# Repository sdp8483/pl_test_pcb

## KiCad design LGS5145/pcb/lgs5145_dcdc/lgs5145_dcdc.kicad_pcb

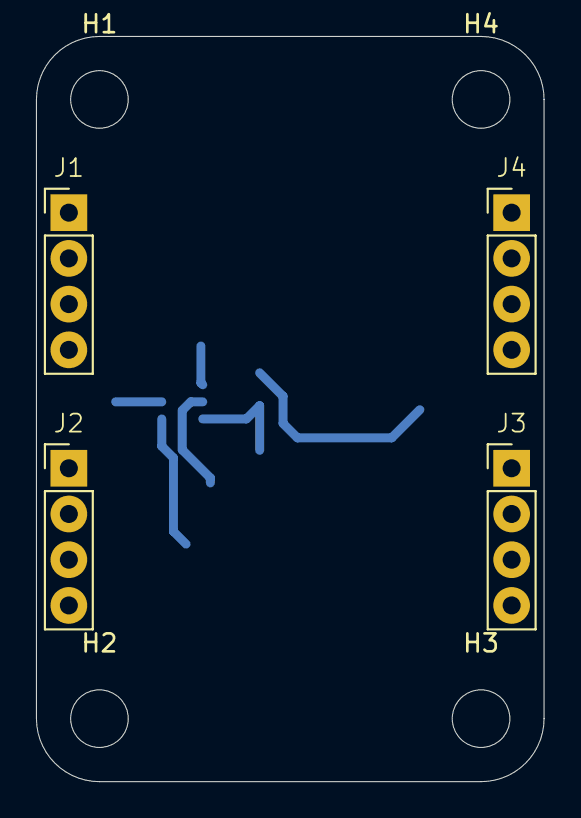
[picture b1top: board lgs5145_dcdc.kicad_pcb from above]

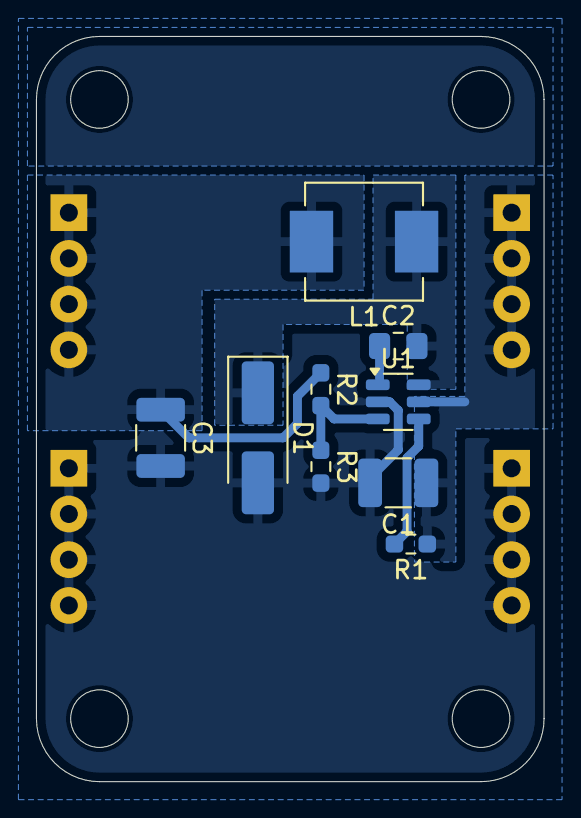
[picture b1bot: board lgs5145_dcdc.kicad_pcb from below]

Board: 2 copper layers, 28.2 x 41.4 mm, 17 parts (9 on the bottom side), 7 nets.

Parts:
C1, C3: 10uF; C_1210_3225Metric_Pad1.33x2.70mm_HandSolder
C2: 100nF; C_0805_2012Metric_Pad1.18x1.45mm_HandSolder
D1: SS56; D_SMA_Handsoldering
H1, H2, H3, H4: MountingHole; MountingHole_3.2mm_M3
J1: IN; PinHeader_1x04_P2.54mm_Vertical
J2, J3: GND; PinHeader_1x04_P2.54mm_Vertical
J4: OUT; PinHeader_1x04_P2.54mm_Vertical
L1: L; L_Vishay_IHLP-2525
R1: 10k; R_0603_1608Metric_Pad0.98x0.95mm_HandSolder
R2: 82k; R_0603_1608Metric_Pad0.98x0.95mm_HandSolder
R3: 16k; R_0603_1608Metric_Pad0.98x0.95mm_HandSolder
U1: LGS5145; SOT-23-6

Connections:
+5V: C3.1, J4.1, J4.2, J4.3, J4.4, L1.2, R2.1
GND: C1.2, C3.2, D1.2 (A), J2.1, J2.2, J2.3, J2.4, J3.1, J3.2, J3.3, J3.4, R3.2, U1.2 (GND)
unnamed: C2.2, D1.1 (K), L1.1, U1.6 (SW)
unnamed: C2.1, U1.1 (BST)
unnamed: R1.2, U1.4 (EN)
unnamed: R2.2, R3.1, U1.3 (FB)
VCC: C1.1, J1.1, J1.2, J1.3, J1.4, R1.1, U1.5 (Vin)

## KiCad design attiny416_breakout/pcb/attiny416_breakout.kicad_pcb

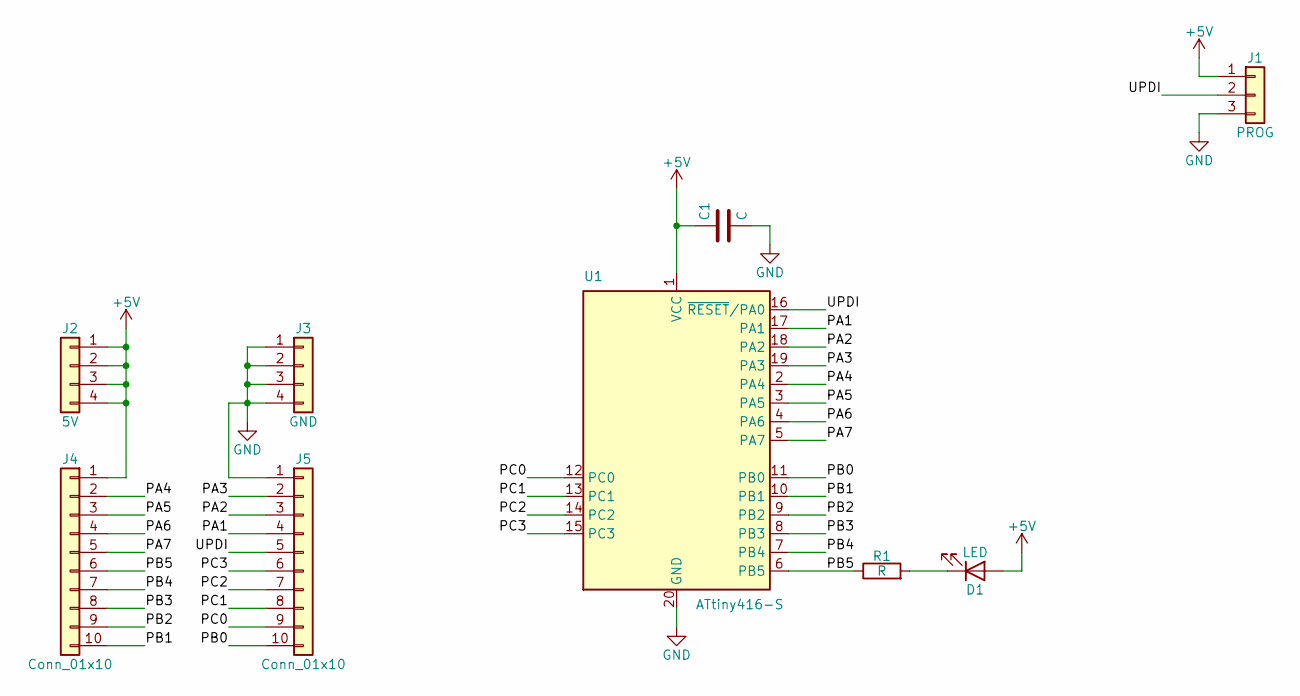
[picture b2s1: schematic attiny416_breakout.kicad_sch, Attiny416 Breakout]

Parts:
C1: C; C_Rect_L7.0mm_W2.0mm_P5.00mm
D1: LED; LED_D5.0mm
J1: PROG; PinHeader_1x03_P2.54mm_Vertical
J2: 5V; PinHeader_1x04_P2.54mm_Vertical
J3: GND; PinHeader_1x04_P2.54mm_Vertical
J4, J5: Conn_01x10; PinHeader_1x10_P2.54mm_Vertical
R1: R; R_0603_1608Metric_Pad0.98x0.95mm_HandSolder
U1: ATtiny416-S; SOIC-20W_7.5x12.8mm_P1.27mm

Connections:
+5V: C1.1, D1.2 (A), J1.1, J2.1, J2.2, J2.3, J2.4, J4.1, U1.1 (VCC)
/PA1: J5.4, U1.17 (PA1)
/PA2: J5.3, U1.18 (PA2)
/PA3: J5.2, U1.19 (PA3)
/PA4: J4.2, U1.2 (PA4)
/PA5: J4.3, U1.3 (PA5)
/PA6: J4.4, U1.4 (PA6)
/PA7: J4.5, U1.5 (PA7)
/PB0: J5.10, U1.11 (PB0)
/PB1: J4.10, U1.10 (PB1)
/PB2: J4.9, U1.9 (PB2)
/PB3: J4.8, U1.8 (PB3)
/PB4: J4.7, U1.7 (PB4)
/PB5: J4.6, R1.1, U1.6 (PB5)
/PC0: J5.9, U1.12 (PC0)
/PC1: J5.8, U1.13 (PC1)
/PC2: J5.7, U1.14 (PC2)
/PC3: J5.6, U1.15 (PC3)
/UPDI: J1.2, J5.5, U1.16 (~RESET/PA0)
GND: C1.2, J1.3, J3.1, J3.2, J3.3, J3.4, J5.1, U1.20 (GND)
unnamed: D1.1 (K), R1.2

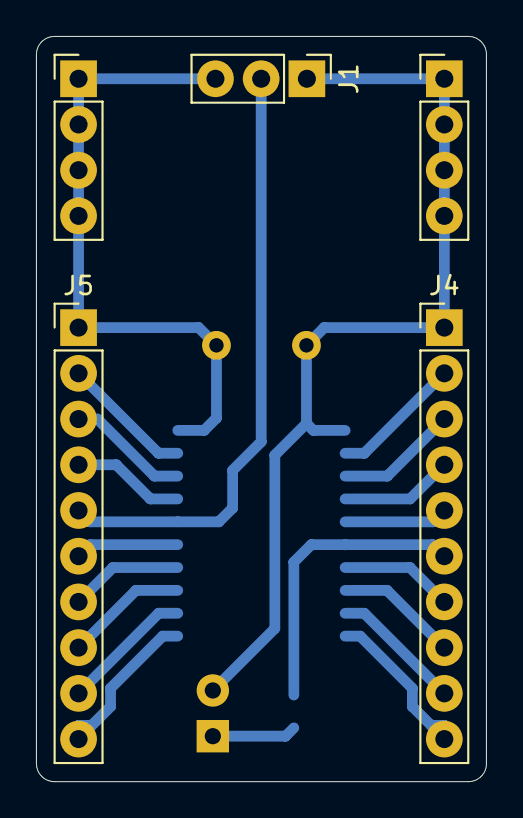
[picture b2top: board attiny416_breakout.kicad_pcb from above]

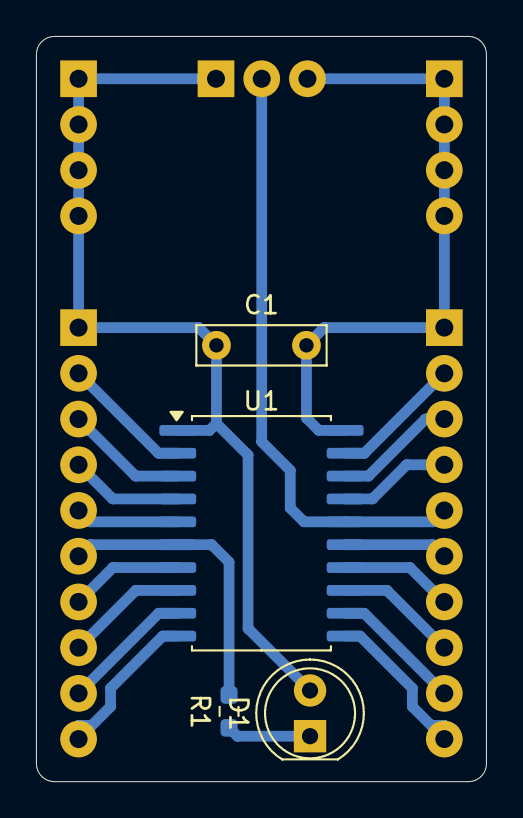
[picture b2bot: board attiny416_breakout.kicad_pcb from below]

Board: 2 copper layers, 25.0 x 41.4 mm, 9 parts (4 on the bottom side), 21 nets.

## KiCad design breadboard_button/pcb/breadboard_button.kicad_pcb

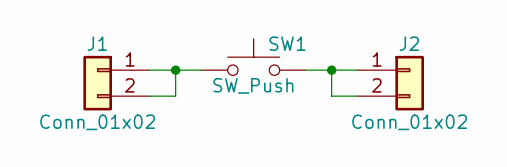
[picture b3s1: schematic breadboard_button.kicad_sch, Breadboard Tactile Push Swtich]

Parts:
J1, J2: Conn_01x02; PinHeader_1x02_P2.54mm_Vertical
SW1: SW_Push; SW_PUSH_6mm

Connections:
unnamed: J1.1, J1.2, SW1.1
unnamed: J2.1, J2.2, SW1.2

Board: 2 copper layers, 3 parts (2 on the bottom side), 2 nets, no tracks yet.

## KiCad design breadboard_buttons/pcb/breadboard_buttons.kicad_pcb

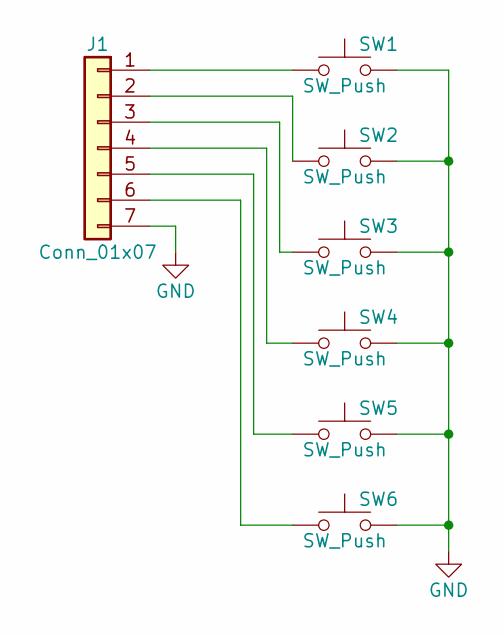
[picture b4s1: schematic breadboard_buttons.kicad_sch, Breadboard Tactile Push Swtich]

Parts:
J1: Conn_01x07; PinHeader_1x07_P2.54mm_Vertical
SW1, SW2, SW3, SW4, SW5, SW6: SW_Push; push_button_6mm_2pin

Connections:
GND: J1.7, SW1.2, SW2.2, SW3.2, SW4.2, SW5.2, SW6.2
unnamed: J1.1, SW1.1
unnamed: J1.2, SW2.1
unnamed: J1.3, SW3.1
unnamed: J1.4, SW4.1
unnamed: J1.5, SW5.1
unnamed: J1.6, SW6.1

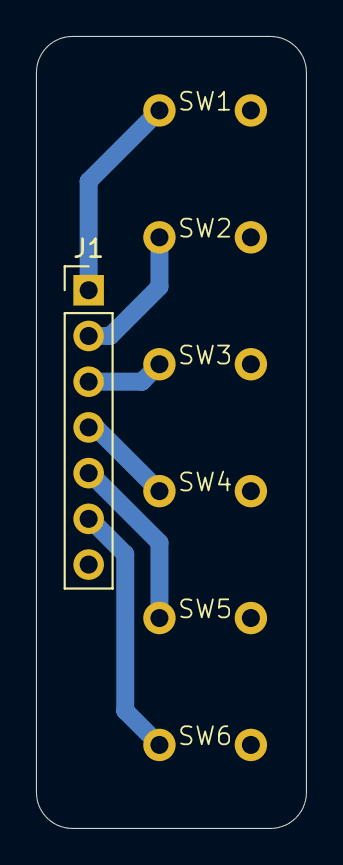
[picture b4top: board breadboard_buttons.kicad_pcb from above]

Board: 2 copper layers, 15.0 x 44.0 mm, 7 parts (0 on the bottom side), 7 nets.

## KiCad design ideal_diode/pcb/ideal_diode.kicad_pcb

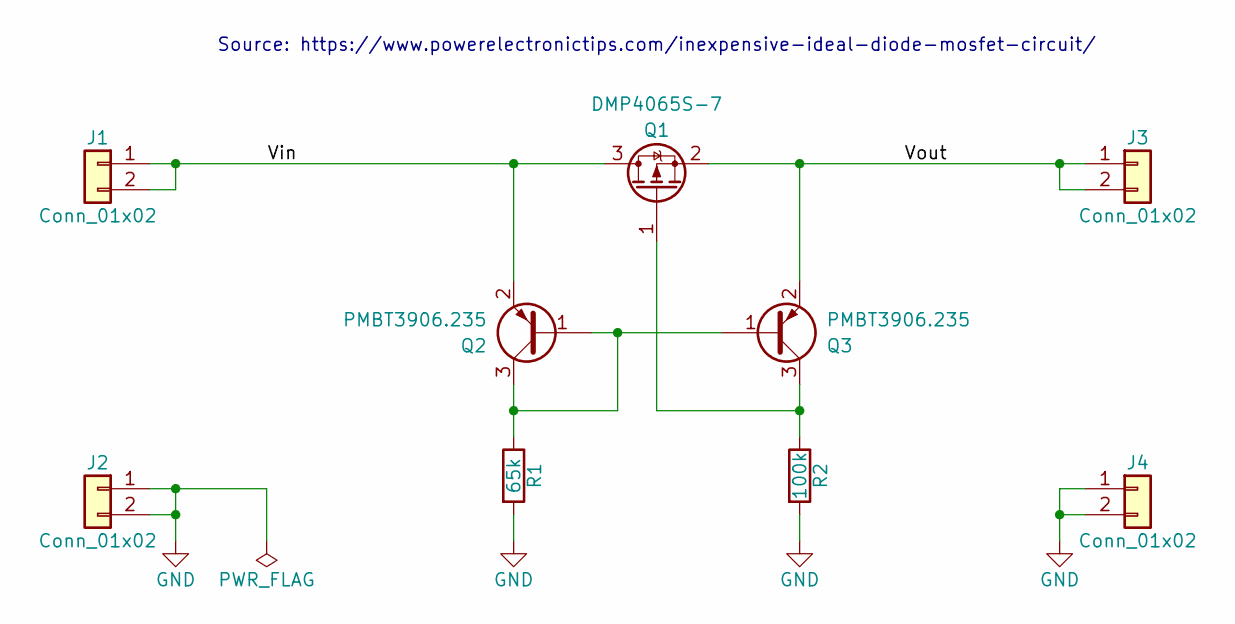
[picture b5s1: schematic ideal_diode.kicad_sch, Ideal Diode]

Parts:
J1, J2, J3, J4: Conn_01x02; PinHeader_1x02_P2.54mm_Vertical
Q1: DMP4065S-7; SOT-23_Handsoldering
Q2, Q3: PMBT3906.235; SOT-23_Handsoldering
R1: 65k; R_0805_2012Metric_Pad1.20x1.40mm_HandSolder
R2: 100k; R_0805_2012Metric_Pad1.20x1.40mm_HandSolder

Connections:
/Vin: J1.1, J1.2, Q1.3 (D), Q2.2 (E)
/Vout: J3.1, J3.2, Q1.2 (S), Q3.2 (E)
GND: J2.1, J2.2, J4.1, J4.2, R1.2, R2.2
unnamed: Q1.1 (G), Q3.3 (C), R2.1
unnamed: Q2.1 (B), Q2.3 (C), Q3.1 (B), R1.1

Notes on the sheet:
Source: https://www.powerelectronictips.com/inexpensive-ideal-diode-mosfet-circuit/

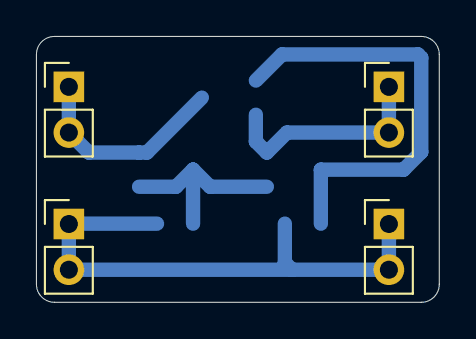
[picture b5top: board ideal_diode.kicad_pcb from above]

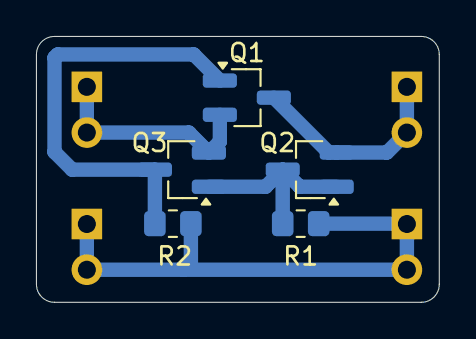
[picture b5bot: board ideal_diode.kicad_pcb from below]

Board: 2 copper layers, 22.4 x 14.8 mm, 9 parts (5 on the bottom side), 5 nets.

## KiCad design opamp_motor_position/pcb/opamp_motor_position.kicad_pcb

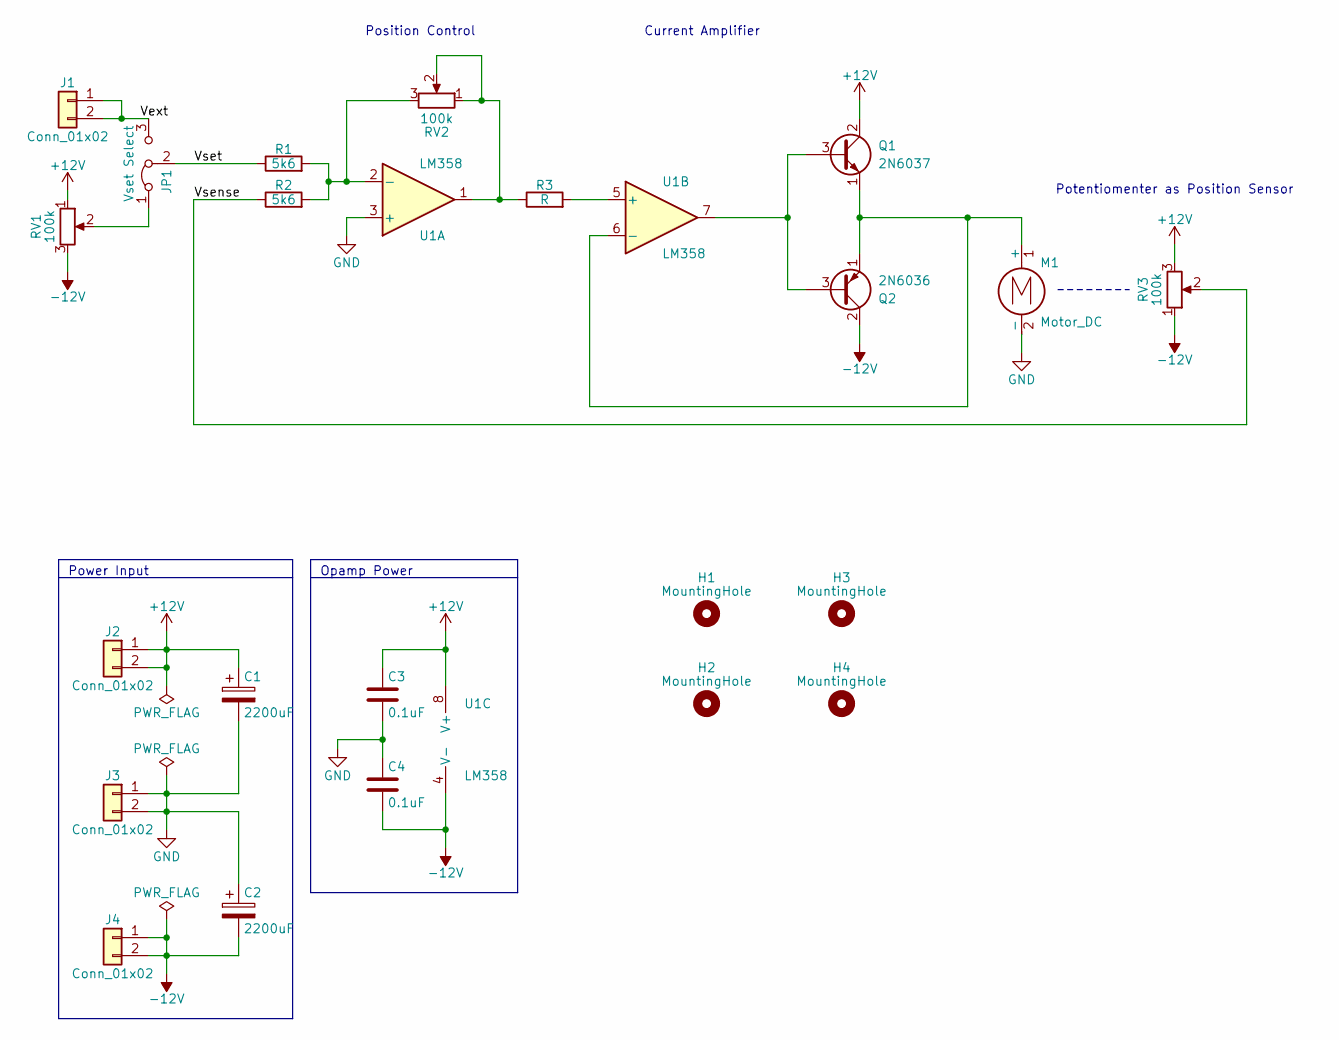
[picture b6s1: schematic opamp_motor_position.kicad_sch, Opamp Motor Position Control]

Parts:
C1, C2: 2200uF; CP_Radial_D12.5mm_P5.00mm
C3, C4: 0.1uF; C_Rect_L7.0mm_W2.0mm_P5.00mm
H1, H2, H3, H4: MountingHole; MountingHole_3.2mm_M3_Pad_TopBottom
J1, J2, J3, J4: Conn_01x02; PinHeader_1x02_P2.54mm_Vertical
JP1: Vset Select; PinHeader_1x03_P2.54mm_Vertical
M1: Motor_DC; Altech_AK100_1x02_P5.00mm
Q1: 2N6037; TO-126-3_Vertical
Q2: 2N6036; TO-126-3_Vertical
R1, R2: 5k6; R_Axial_DIN0309_L9.0mm_D3.2mm_P12.70mm_Horizontal
R3: R; R_Axial_DIN0309_L9.0mm_D3.2mm_P12.70mm_Horizontal
RV1, RV2, RV3: 100k; Potentiometer_Alps_RK163_Single_Horizontal
U1: LM358; DIP-8_W7.62mm_LongPads

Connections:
+12V: C1.1, C3.1, J2.1, J2.2, Q1.2 (C), RV1.1, RV3.3, U1.8 (V+)
-12V: C2.2, C4.2, J4.1, J4.2, Q2.2 (C), RV1.3, RV3.1, U1.4 (V-)
/Vext: J1.1, J1.2, JP1.3 (B)
/Vsense: R2.1, RV3.2
/Vset: JP1.2 (C), R1.1
GND: C1.2, C2.1, C3.2, C4.1, J3.1, J3.2, M1.2 (-), U1.3 (+)
unnamed: JP1.1 (A), RV1.2
unnamed: M1.1 (+), Q1.1 (E), Q2.1 (E), U1.6 (-)
unnamed: Q1.3 (B), Q2.3 (B), U1.7
unnamed: R3.1, RV2.1, RV2.2, U1.1
unnamed: R1.2, R2.2, RV2.3, U1.2 (-)
unnamed: R3.2, U1.5 (+)

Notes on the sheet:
Opamp Power
Current Amplifier
Potentiomenter as Position Sensor
Power Input
Position Control

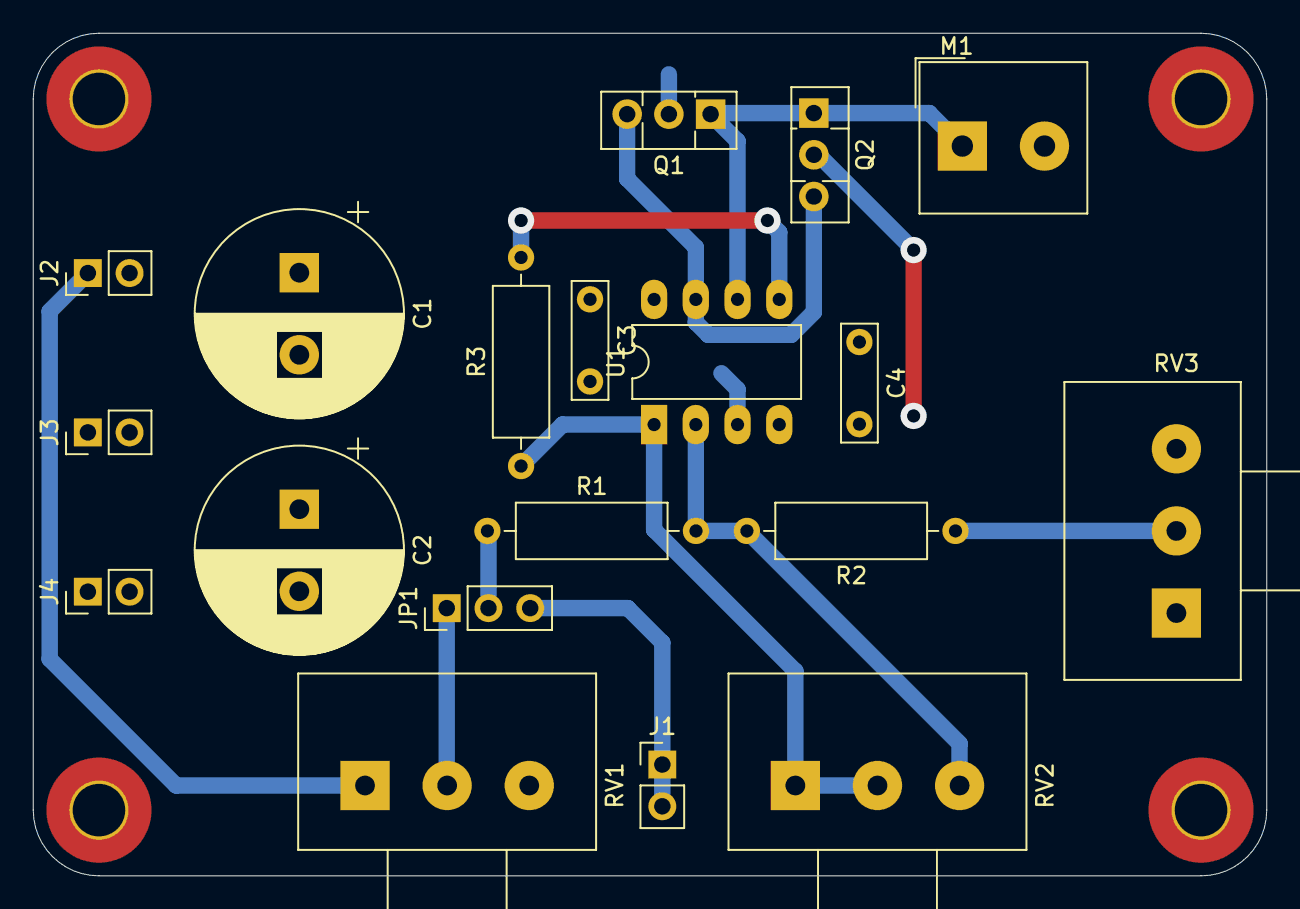
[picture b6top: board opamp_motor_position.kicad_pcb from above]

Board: 2 copper layers, 75.1 x 51.3 mm, 23 parts (0 on the bottom side), 12 nets.

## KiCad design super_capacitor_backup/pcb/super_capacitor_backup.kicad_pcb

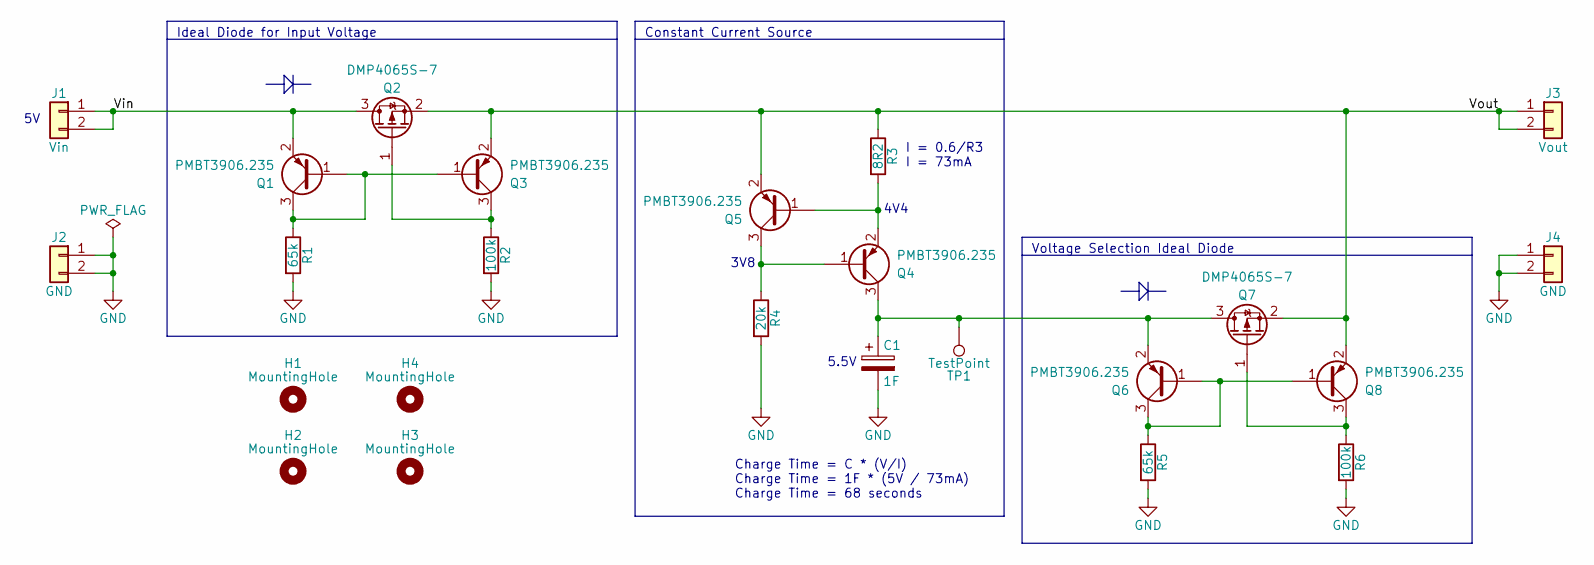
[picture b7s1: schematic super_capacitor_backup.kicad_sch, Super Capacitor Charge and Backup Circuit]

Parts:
C1: 1F; CP_Radial_D20.0mm_P5.00mm
H1, H2, H3, H4: MountingHole; MountingHole_3.2mm_M3
J1: Vin; PinHeader_1x02_P2.54mm_Vertical
J2, J4: GND; PinHeader_1x02_P2.54mm_Vertical
J3: Vout; PinHeader_1x02_P2.54mm_Vertical
Q1, Q3, Q4, Q5, Q6, Q8: PMBT3906.235; SOT-23_Handsoldering
Q2, Q7: DMP4065S-7; SOT-23_Handsoldering
R1, R5: 65k; R_0805_2012Metric_Pad1.20x1.40mm_HandSolder
R2, R6: 100k; R_0805_2012Metric_Pad1.20x1.40mm_HandSolder
R3: 8R2; R_1206_3216Metric_Pad1.30x1.75mm_HandSolder
R4: 20k; R_0805_2012Metric_Pad1.20x1.40mm_HandSolder
TP1: TestPoint; TestPoint_Loop_D1.80mm_Drill1.0mm_Beaded

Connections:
/Vin: J1.1, J1.2, Q1.2 (E), Q2.3 (D)
/Vout: J3.1, J3.2, Q2.2 (S), Q3.2 (E), Q5.2 (E), Q7.2 (S), Q8.2 (E), R3.1
GND: C1.2, J2.1, J2.2, J4.1, J4.2, R1.2, R2.2, R4.2, R5.2, R6.2
unnamed: Q1.1 (B), Q1.3 (C), Q3.1 (B), R1.1
unnamed: Q2.1 (G), Q3.3 (C), R2.1
unnamed: Q4.1 (B), Q5.3 (C), R4.1
unnamed: C1.1, Q4.3 (C), Q6.2 (E), Q7.3 (D), TP1.1
unnamed: Q4.2 (E), Q5.1 (B), R3.2
unnamed: Q6.1 (B), Q6.3 (C), Q8.1 (B), R5.1
unnamed: Q7.1 (G), Q8.3 (C), R6.1

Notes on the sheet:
4V4
Ideal Diode for Input Voltage
Voltage Selection Ideal Diode
3V8
I = 0.6/R3 I = 73mA
Constant Current Source
Charge Time = C * (V/I) Charge Time = 1F * (5V / 73mA) Charge Time = 68 seconds
5.5V

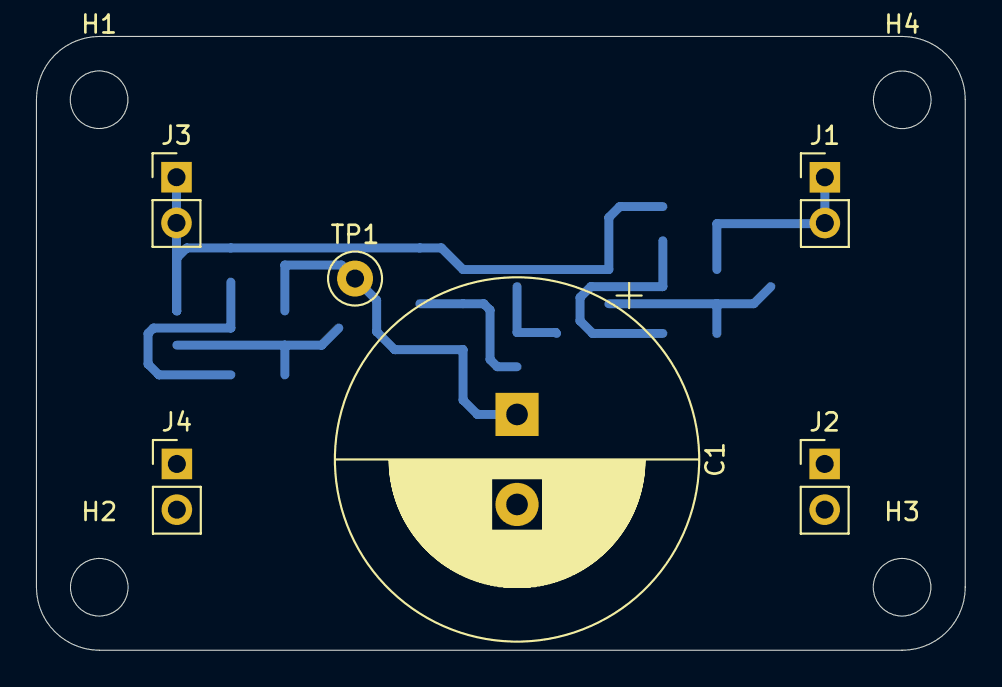
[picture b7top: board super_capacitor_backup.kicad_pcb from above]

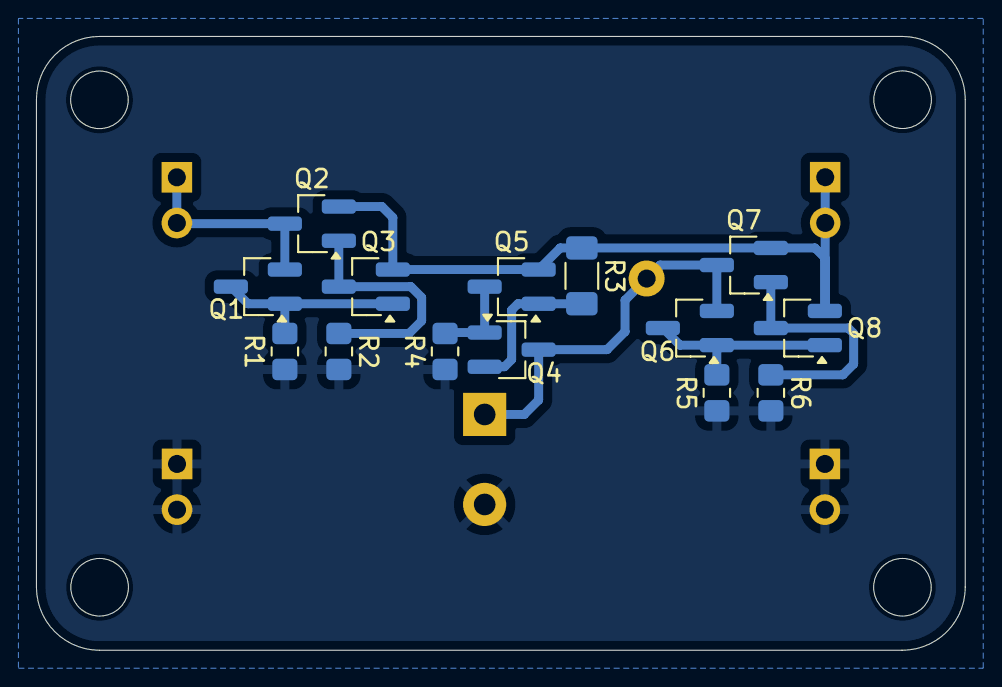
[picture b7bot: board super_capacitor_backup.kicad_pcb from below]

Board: 2 copper layers, 51.6 x 34.1 mm, 24 parts (14 on the bottom side), 10 nets.

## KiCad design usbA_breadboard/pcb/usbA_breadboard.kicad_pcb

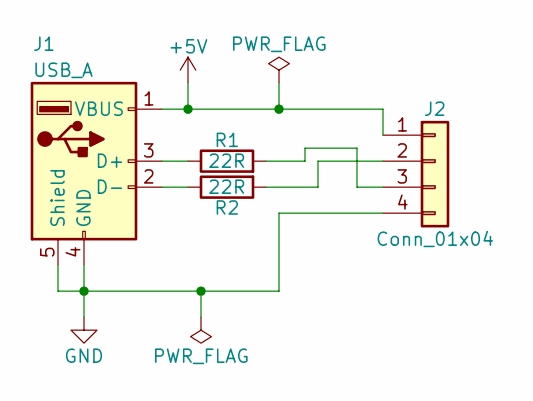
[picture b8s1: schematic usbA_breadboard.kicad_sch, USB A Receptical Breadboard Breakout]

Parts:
J1: USB_A; USB_A_CONNFLY_DS1095-WNR0
J2: Conn_01x04; PinHeader_1x04_P2.54mm_Vertical
R1, R2: 22R; R_Axial_DIN0207_L6.3mm_D2.5mm_P10.16mm_Horizontal

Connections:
+5V: J1.1 (VBUS), J2.1
GND: J1.4 (GND), J1.5 (Shield), J2.4
unnamed: J1.3 (D+), R1.1
unnamed: J1.2 (D-), R2.1
unnamed: J2.2, R2.2
unnamed: J2.3, R1.2

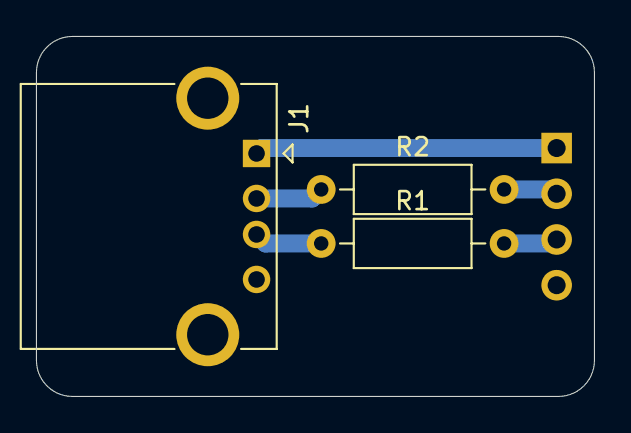
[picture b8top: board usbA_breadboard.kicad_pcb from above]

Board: 2 copper layers, 31.0 x 20.0 mm, 4 parts (1 on the bottom side), 6 nets.
